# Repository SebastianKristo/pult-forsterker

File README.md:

<h1 align="center">Skjold</h1>

<p align="center"><b>Musikk i alle rom.</b><br>
Forsterkere, spillere og høyttalere som spiller sammen, styrt fra én app.<br>
Åpen programvare. Tegnet og bygget i Norge av Skjold Lab.</p>

<p align="center">
<a href="https://skjold-lab.com/">Nettside</a> ·
<a href="https://github.com/SebastianKristo/pult-forsterker/releases/latest">Last ned</a> ·
<a href="docs/TOTALINSTRUKS.md">Kom i gang</a> ·
<a href="docs/api/intro.md">API</a>
</p>

---

Skjold er et lydsystem du kan bygge selv. Hver enhet er en Raspberry Pi eller ESP32 med Skjold-programvaren, og alle
dukker opp i samme app. Spill det samme i hele huset, eller noe forskjellig i hvert rom.

## Produktene

| | Hva | Bygget på |
|---|---|---|
| **[Skjold S1](https://skjold-lab.com/s1/)** | Streamingforsterker for skrivebordet. 2 × 50 W, 4,58″ skjerm, USB-bryter for to PC-er. | Raspberry Pi 4, TPA3116D2 |
| **[Skjold Node](https://skjold-lab.com/node/)** | Liten nettverksspiller for rom som allerede har forsterker. | Raspberry Pi 4 eller 3B |
| **[Skjold Touch](https://skjold-lab.com/touch/)** | Spiller med 7″ berøringsskjerm. | Raspberry Pi 4, PCM5122 |
| **[Skjold Røst](https://skjold-lab.com/rost/)** | Aktiv høyttaler med grill hele veien rundt, skjerm og volumknott. | ESP32-S3 |
| **[Skjold Stav](https://skjold-lab.com/stav/)** | Fjernkontroll med 2,8″ berøringsskjerm, IR og ladedokk. | ESP32 (ESPHome) |
| **[Skjold Core](https://skjold-lab.com/core/)** | Bare programvaren, på en Raspberry Pi du allerede har. | Raspberry Pi 4 eller 3B |
| **Kassett, Hjul, Radio, Sans** | NFC-kassettspiller, dreieknapp-fjernkontroll, kjøkkenradio og romsensor. | ESP32 / Raspberry Pi |

## Dette kan den

- **Kilder:** AirPlay 2, Spotify Connect, Blåtann, internettradio, AUX og USB-lyd fra PC.
- **Bibliotek:** Navidrome, Plex, YouTube Music og Lyrion Music Server.
- **Flere rom:** synkron avspilling og grupper, med volum per rom.
- **Lyd:** equalizer per kilde, loudness og romkorreksjon med mikrofonen i telefonen.
- **Smarthus:** Home Assistant, Homey, Apple Hjem, Matter og MQTT. Enhetene finnes automatisk på nettverket.
- **Styring:** app for iPhone og Android, nettleser, knappene på enheten, fjernkontroll eller API.

## Kom i gang

1. **Last ned [Skjold Flasher](https://github.com/SebastianKristo/pult-forsterker/releases/latest)** for Mac, Windows eller Linux.
2. **Velg enhet** (S1, Touch, Node eller Core), skriv inn Wi-Fi og navn, og skriv SD-kortet.
3. **Sett kortet i Raspberry Pi-en.** Første oppstart installerer Skjold. Det tar 15–20 minutter.
4. **Åpne appen** eller `http://<navn>.local:8765` i nettleseren.

Hele veien fra SD-kort til smarthus står i [docs/TOTALINSTRUKS.md](docs/TOTALINSTRUKS.md).

Vil du installere for hånd på en ferdig Raspberry Pi OS?

```bash
git clone https://github.com/SebastianKristo/pult-forsterker.git && cd pult-forsterker
```

```bash
KI_AMP_BOARD=node bash pi/install.sh
```

Bytt `node` med `main` (S1), `touch` eller bruk `KI_AMP_CORE=1` for Core. Alle valgene står øverst i [`pi/install.sh`](pi/install.sh).

## Last ned

Alt ligger samlet i [siste utgivelse](https://github.com/SebastianKristo/pult-forsterker/releases/latest):

- **Skjold Flasher** (`.dmg`, `.exe`, `.AppImage`)
- **Android-appen** (`.apk`) og **iOS-appen** (usignert `.ipa`)
- **Filer til 3D-printer:** `skjold-3d-print.zip` med én mappe per produkt. Hver mappe har ferdige plater for Creality K2 (`.3mf`), enkeltdeler (STL), kilde (OpenSCAD) og egen `LES_MEG.md`
- **Bruksanvisning** (PDF) og **fastvare** for Røst

## Hva som ligger hvor

| Mappe | Innhold |
|---|---|
| [`pi/`](pi/) | Forsterkerprogrammet (`ki_amp_daemon.py`), installasjon, oppdatering og tester |
| [`skjold/app/`](skjold/app/) | Web-appen (Preact) og skjermbildet til Touch |
| [`skjold/ios/`](skjold/ios/), [`skjold/android/`](skjold/android/) | Appene for iPhone (SwiftUI) og Android (Compose) |
| [`skjold/flasher/`](skjold/flasher/) | Skjold Flasher (Electron) |
| [`skjold/os/`](skjold/os/) | Skjermprogrammet på S1 og Node |
| [`skjold/nettside/`](skjold/nettside/) | Nettsiden |
| [`kabinett/`](kabinett/) | 3D-modeller og utskriftsfiler. Hvert produkt har sin `LES_MEG.md` |
| [`pcb/`](pcb/), [`esphome/`](esphome/) | Kretskort og ESPHome-oppsett |
| [`custom_components/skjold/`](custom_components/skjold/), [`ha-kort/`](ha-kort/) | Home Assistant-integrasjonen og kortet (HACS) |
| [`homey/`](homey/) | Homey-appen |
| [`docs/`](docs/) | Veiledninger og [API-dokumentasjon](docs/api/intro.md) |

Flere veiledninger: [Skjold Touch](docs/SKJOLD_TOUCH.md) · [Oppsett-nett](docs/OPPSETT_NETT.md) · [Flere rom](docs/MULTIROOM.md) · [Skjold-hjem](docs/SKJOLD_HJEM.md) ·
[Fjernstyring](docs/FJERNSTYRING.md) · [Plugins](docs/PLUGINS.md) · [Proxmox og vanlig PC](docs/PROXMOX.md) ·
[Den første pultforsterkeren](docs/PULTFORSTERKER.md)

## Utvikling

```bash
cd pi && python3 -m pytest -q tests
```

```bash
cd skjold/app && npm ci && npm run dev
```

Web-appen kan kjøres mot en falsk enhet: `python3 skjold/ios/ci/mock_skjold.py 8765`, og åpne
`http://localhost:5173/?host=http://127.0.0.1:8765`.

## Status

Skjold er et byggeprosjekt og er ikke til salgs. Programvaren er i daglig bruk, men ikke alt er testet på alle
kombinasjoner av maskinvare. Finner du en feil, [meld den her](https://github.com/SebastianKristo/pult-forsterker/issues).

## Lisens

- **Programvare** (`pi/`, `skjold/app`, `skjold/os`, `skjold/flasher`, integrasjonene): MIT. Se [LICENSE](LICENSE).
- **Maskinvare, design og dokumentasjon** (`pcb/`, `kabinett/`, `skjold/design/` m.m.): CC BY-NC-SA 4.0. Du kan bygge
  selv, men ikke for salg. Se [LISENS-MASKINVARE.md](LISENS-MASKINVARE.md).
- **Nettsiden** (`skjold/nettside/`): alle rettigheter forbeholdt.

Full oversikt står i [LISENS.md](LISENS.md). Kommersiell lisens: jemtlands@proton.me

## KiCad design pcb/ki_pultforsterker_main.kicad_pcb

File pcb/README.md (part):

# Pultforsterker – hovedkort rev B

Ett kort (180 × 100 mm, 2 lag) som erstatter alle modulene, og som i tillegg har USB-delingsswitch, to AUX-innganger som
digitaliseres (så alt kan mikses), «smart relé» for strømmen til forsterkerdelen, hodetelefonutgang i fronten med
auto-demping, og plass til en 2,8" SPI-TFT med touch.
Raspberry Pi 4 kobles til med 40-pinners flatkabel; frontdelene med JST XH-plugger; alle bakkontakter er panelmonterte med
korte kabler til kortet.

**Status: rev B er ikke prøvd i praksis.** Kortet er tegnet og autorutet med KiCad 7 og Freerouting, DRC er fri for koblings- og
klaringsfeil, men ingen har bygget det. Regn med at første utgave kan trenge en jumper eller to. Programvaren for rev B (I2S-slave,
MCP23017, per-kilde-nivå, TFT) er skrevet, men kan bare testes på et ferdig kort.

## Blokker

| Blokk | Krets | Merknad |
|---|---|---|
| 24 V inn | skruterminal → sikring 5 A (5×20, THT) → reverspolaritets-FET → TVS SMBJ28A → 2 × 680–1000 µF/35 V Ø10 (THT, maks 16 mm høye) | KCD1 hovedbryter i serie utenfor kortet |
| 5 V / 5 A (alltid) | TPS54560 buck, 400 kHz, 10 µH, 3 × 47 µF, satt til 5,06 V (33k/6,2k) | Pi 4 («5V PI»), USB-hub, relé-spole |
| **Smart relé** | SRD-05VDC-SL-C (24 V → forsterker) + AO3401 P-MOSFET (5 V → 5V_SW) fra GPIO 27 via AO3400 | 5V_SW: LED-ringer, ADC-analog, TFT-baklys (PGA2311 og hodetelefonforsterkeren er alltid på, men mutet i standby). Av = helt stille og mørkt. Knapp bak på GPIO 15 |
| 3,3 V (alltid) | AMS1117-3.3 | MCP23017, pull-ups, encoder, **DAC, ADC-digital, oscillator, OLED og TFT-logikk** (Pi-ens I2C/SPI/I2S må aldri drive inn i strømløse kretser; skjermen slukkes i programvare) |
| 3,3 V_SW | AMS1117-3.3 fra 5V_SW | bare TFT-baklyset (Q9/Q10) |
| −5 V | LM2662 (FC = V+, 150 kHz) fra alltid-på 5 V, 10 µF inn/fly/ut | PGA2311 VA− (10–12 mA) |
| DAC | PCM5102A, I2S-slave, SCK = GND (intern PLL), FLT/DEMP/FMT = GND, XSMT fra GPIO 26 | 100 Ω + 2,2 nF ut |
| **ADC AUX 1** | PCM1808, I2S-master 256 fs fra 12,288 MHz-oscillator (48 kHz) | Pi-en er I2S-slave. Inngang 10k/10k-deler, 4,7 µF, 1 kΩ + 1 nF |
| **USB-kodek AUX 2** | PCM2900C, 12 MHz-krystall, bus-powered fra en USB-port på Pi-en (J19) | Inngang 10k/4,7k-deler, 4,7 µF. Vises som «USB Audio CODEC» |
| Volum | PGA2311 (±5 V), bit-banget fra GPIO 0 (SDI), 1 (SCLK), 16 (CS) – header 27/28/36, 5 V via ferritt + 10 µF | fast nivå; volum og nivå per kilde gjøres digitalt |
| Forsterker | TPA3116D2DAD, 26 dB (100k/20k), BD-modus (MODSEL = GND), 400 kHz (AM = 000), MUTE = GND, SYNC åpen, PLIMIT = GVDD, 10 µH + 680 nF + snubber per utgang | **Kjøleflaten er på toppen**: ingen loddepasta under, kjøleribbe 20 × 20 limes på. SDZ fra GPIO 22 |
| **USB-switch** | FE1.1s 4-ports hub + TS3USB221 2:1-mux (OE = GND). 2 × USB-C (PC 1/PC 2) på kortet, 4 × USB-A i venstre kant, polyfuse 2 A | Mux-valg fra MCP23017 GPB4 (S lav = PC 1). CC-pinnene har 5,1 k, så USB-C–USB-C-kabel virker. Huben og muxen går på alltid-5 V |
| I/O-ekspander | MCP23017 (I2C 0x20), INT → GPIO 14 | GPA0-4 knapper AIR/BT/AUX/USB/PWR, GPA5 jack-deteksjon, GPA6 HP-EN, GPB0-3 LED-ringer, GPB4 USB-mux, **GPB5 overtemperatur (NTC)**; GPA7 ligger på «EXP» men kan bare brukes som utgang (Microchip-errata: GPA7/GPB7 er ikke innganger) |
| **Overtemperaturvakt** | NTC 10 k (B 3950) på kjøleribben → J24 → 3,3 k-deler → 74LVC1G14 Schmitt-inverter (U14) → MCP GPB5. 100 k pull-down så «kald» hvis U14 mangler | Vipper ved ca. 75 °C, tilbake ved ca. 50 °C. Daemonen demper TPA3116 (SDZ) mens den er varm og melder i loggen/`/api/state` (`overtemp`) |
| LED-ringer | 5 × AO3400 low-side | POWER-ring på GPIO 12 (PWM) |
| **Hodetelefoner** | TPA6132A2 (DirectPath, +6 dB) etter PGA2311, 1 µF inn, alltid-på 5 V (EN kommer fra alltid-på MCP, og må aldri være høyere enn VDD). EN fra MCP23017 GPA6; jack-bryteren (DET) via 10 k til GPA5, 10 k pulldown på OUTL gir sikker «lav» uten plugg | 3,5 mm PJ-392 i fronten under POWER (J23). Ved innplugging dempes TPA3116 (SDZ) – kan slås av i HA/Homey |
| TFT | 14-pinners header (standard 2,4"/2,8" ILI9341/ST7789V-modul med XPT2046) | SPI0 CE0 (GPIO 8) = TFT, CE1 (GPIO 7) = touch med 10 k pull-up, DC 5, RST 6, IRQ 17, baklys GPIO 13 (PWM) via AO3400 + AO3401 fra 3V3_SW |

## GPIO-kart (hovedkort rev B)

| GPIO | Bruk | GPIO | Bruk |
|---|---|---|---|
| 2, 3 | I2C: OLED, MCP23017 | 18, 19, 21, 20 | I2S BCK, LRCK, DAC-data, ADC-data (Pi er slave) |
| 4 | OLED RES | 22 | TPA3116 SDZ (høy = på) |
| 5, 6, 13 | TFT DC, RST, baklys (PWM) | 23, 24, 25 | encoder CLK, DT, SW |
| 7, 8 | SPI0 CE1 touch, CE0 TFT | 26 | DAC XSMT |
| 0, 1 (header 27/28) | PGA2311 SDI, SCLK (ID-EEPROM-pinnene – ingen HAT-EEPROM på kortet) | 16 | PGA2311 CS |
| 9, 10, 11 | SPI0 MISO (bare touch – TFT-ens SDO er ikke koblet), MOSI, SCLK | 27 | strømrelé + 5V_SW |
| 12 | POWER-ring (PWM) | | |
| 14 | MCP23017 INT | 15 | strømknapp bak |
| 17 | touch IRQ | | |

Sett `KI_AMP_BOARD=main` i `/etc/ki-amp.env` (gjøres av `KI_AMP_BOARD=main bash install.sh`).

## Kontakter

| Ref | Type | Pinner |
|---|---|---|
| J1 | skruterminal 5,08 | 24 V +, GND (fra DC-099 via KCD1) |
| J2 / J3 | skruterminal 5,08 | SPK L + −, SPK R + − |
| J4 / J20 | JST XH 3 | AUX 1 / AUX 2: L, R, GND (fra PJ392 bak) |
| J5 | 2×20 header | Raspberry Pi 40-pin (flatkabel 15–20 cm). Pi-en skrus under kortet i H5–H8 (M2,5, 20 mm avstandsstykker), portene mot høyre |
| J6 | skruterminal 5,08 | 5 V, GND → Pi 4 header pinne 2/6 (18 AWG) |
| J7 | JST XH 6 | knapp 1 «BT» (AirPlay + Bluetooth), knapp 2 «RADIO», AUX, USB, POWER, GND (bryterne) |
| J8 | JST XH 5 | CLK, DT, SW, 3V3, GND (encoder) |
| J9 | JST XH 5 | 3V3_SW, GND, SDA, SCL, RES (OLED) |
| J10 | JST XH 6 | 5V_SW, AIR−, BT−, AUX−, USB−, POWER− (LED-ringer) |
| J11 / J12 | USB-C på kortet, i bakkanten (åpningen mot bakpanelet) | PC 1 / PC 2 → panelmontert USB-C bak; panelkabelens hann-plugg settes rett i, 15–20 cm |
| J13 | 1×14 header 2,54 | TFT: VCC GND CS RST DC MOSI SCK LED (MISO ikke koblet) T_CLK T_CS T_DIN T_DO T_IRQ (samme rekkefølge som modulen) |
| J15–J18 | USB-A | 4 × USB-A ut gjennom venstre vegg |
| J19 | JST XH 4 | 5V, D−, D+, GND fra en USB-A-port på Pi-en (USB-kodeken) |
| J21 | JST XH 2 | strømknapp bak (momentan), GND |
| J22 | JST XH 6 | EXP: MCP GPA5 (= jack-deteksjon via 10 k), GPA6 (= HP-EN), GPA7 (ledig, bare utgang), GPB5 (= overtemperatur fra U14 – ikke driv den), 3V3, GND |
| J24 | JST XH 2 | NTC 10 k (B 3950) festet på kjøleribben (ikke polarisert) |
| J23 | JST XH 4 | Hodetelefonjack i fronten (PJ392 med bryter, under POWER): L, R, GND, DET (jackens bryterkontakt for L: ligger mot L uten plugg, åpen med plugg) |

## Filer

- `build_board.py` – hele kortet (deler, netliste, plassering) som Python mot pcbnew. Kjør for å regenerere `.kicad_pcb`.
- `build_schematic.py` – lager skjemaet `ki_pultforsterker_main.kicad_sch` (ett A1-ark, delene gruppert i blokker, globale etiketter med nettnavnene) fra kortet, pluss egne symboler i `ki_pultforsterker.kicad_sym`; verifiserer netlisten pinne for pinne mot `.kicad_pcb` (må gi 0 avvik), kjører ERC og lager `produksjon/skjema.pdf`/`.svg`. Kjør `python3 build_schematic.py` for å regenerere (etter `build_board.py`/`export.py`).
- `route.py` – eksporterer DSN og kjører Freerouting (`FREEROUTING=/sti/freerouting.jar python3 route.py`).
- `export.py` – importerer SES, fyller GND-soner, kjører DRC, lager `produksjon/`.
- `produksjon/ki_pultforsterker_main_gerber.zip` – last opp til JLCPCB/PCBWay (2 lag, 1,6 mm, HASL eller ENIG, 1 oz).
- `produksjon/ki_pultforsterker_main_bom.csv` + `_cpl.csv` – for SMT-montering (LCSC-numre).
- `bom.csv` – full deleliste per referanse.

## Bestilling

1. JLCPCB → «Add gerber file» → zip-en. 2 lag, 180 × 100 mm, grønn/svart, HASL (lead free).
2. Huk av «PCB Assembly», Top side, 2 stk. Last opp BOM og CPL.
3. Kontroller at alle LCSC-numre finnes på lager; bytt tilsvarende hvis noen er tomme (verdiene står i BOM). Alle koder i BOM-en er
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
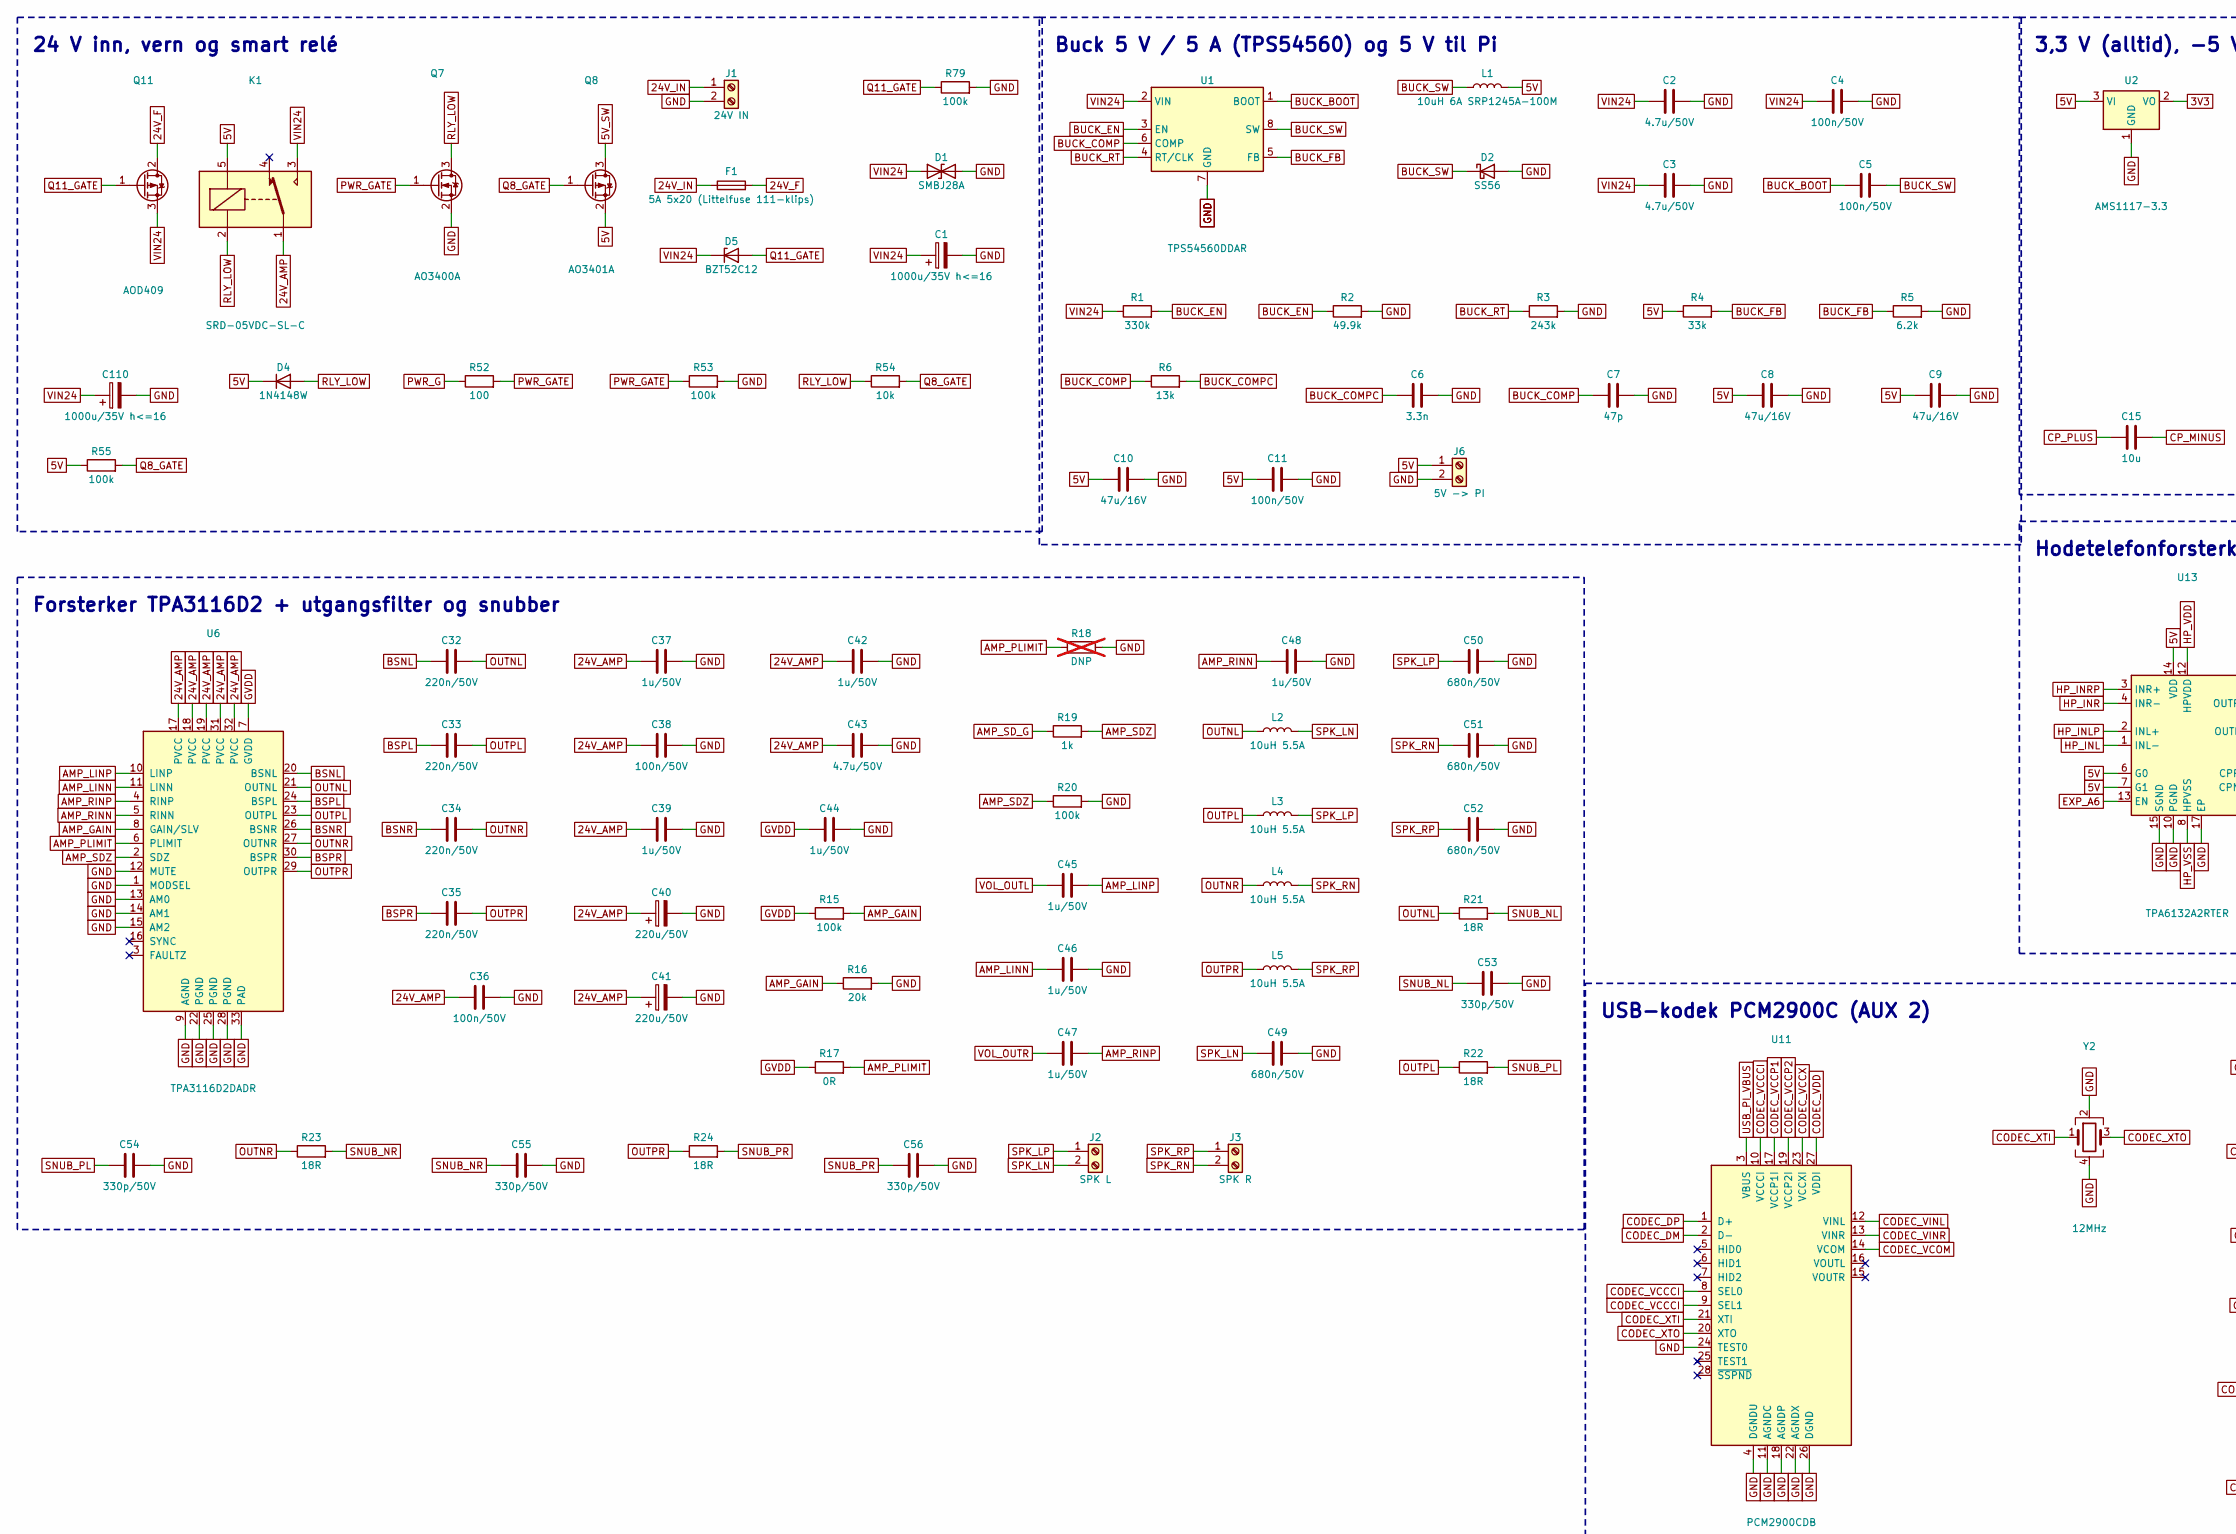
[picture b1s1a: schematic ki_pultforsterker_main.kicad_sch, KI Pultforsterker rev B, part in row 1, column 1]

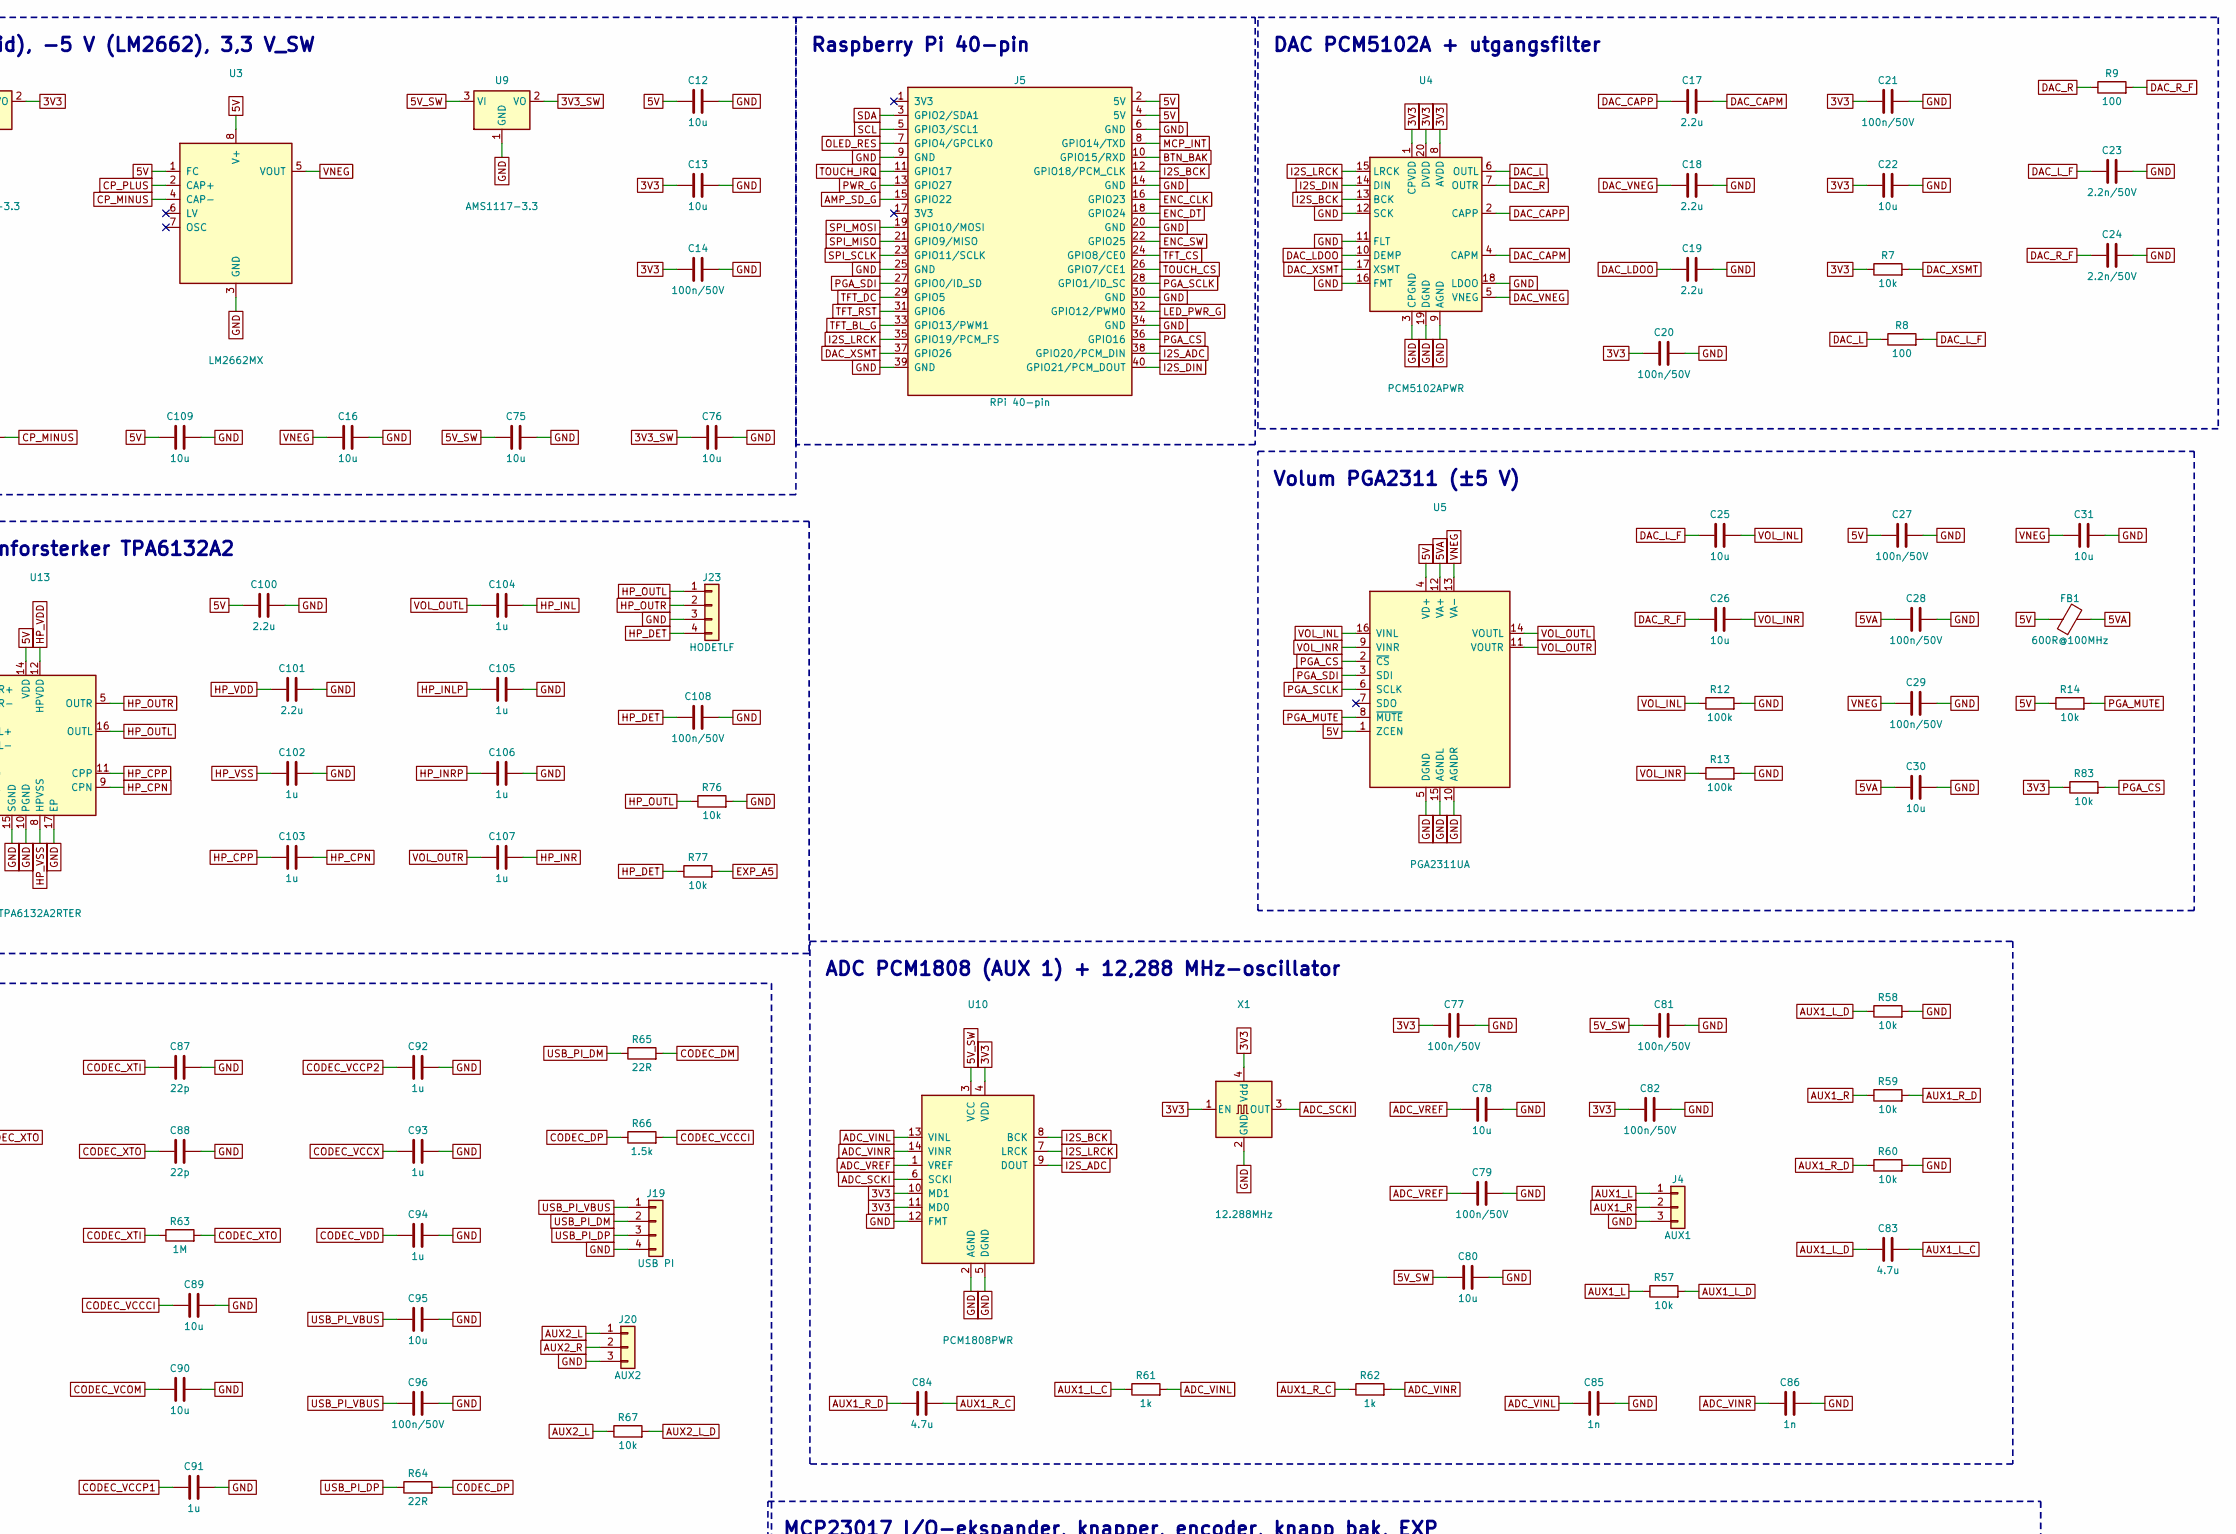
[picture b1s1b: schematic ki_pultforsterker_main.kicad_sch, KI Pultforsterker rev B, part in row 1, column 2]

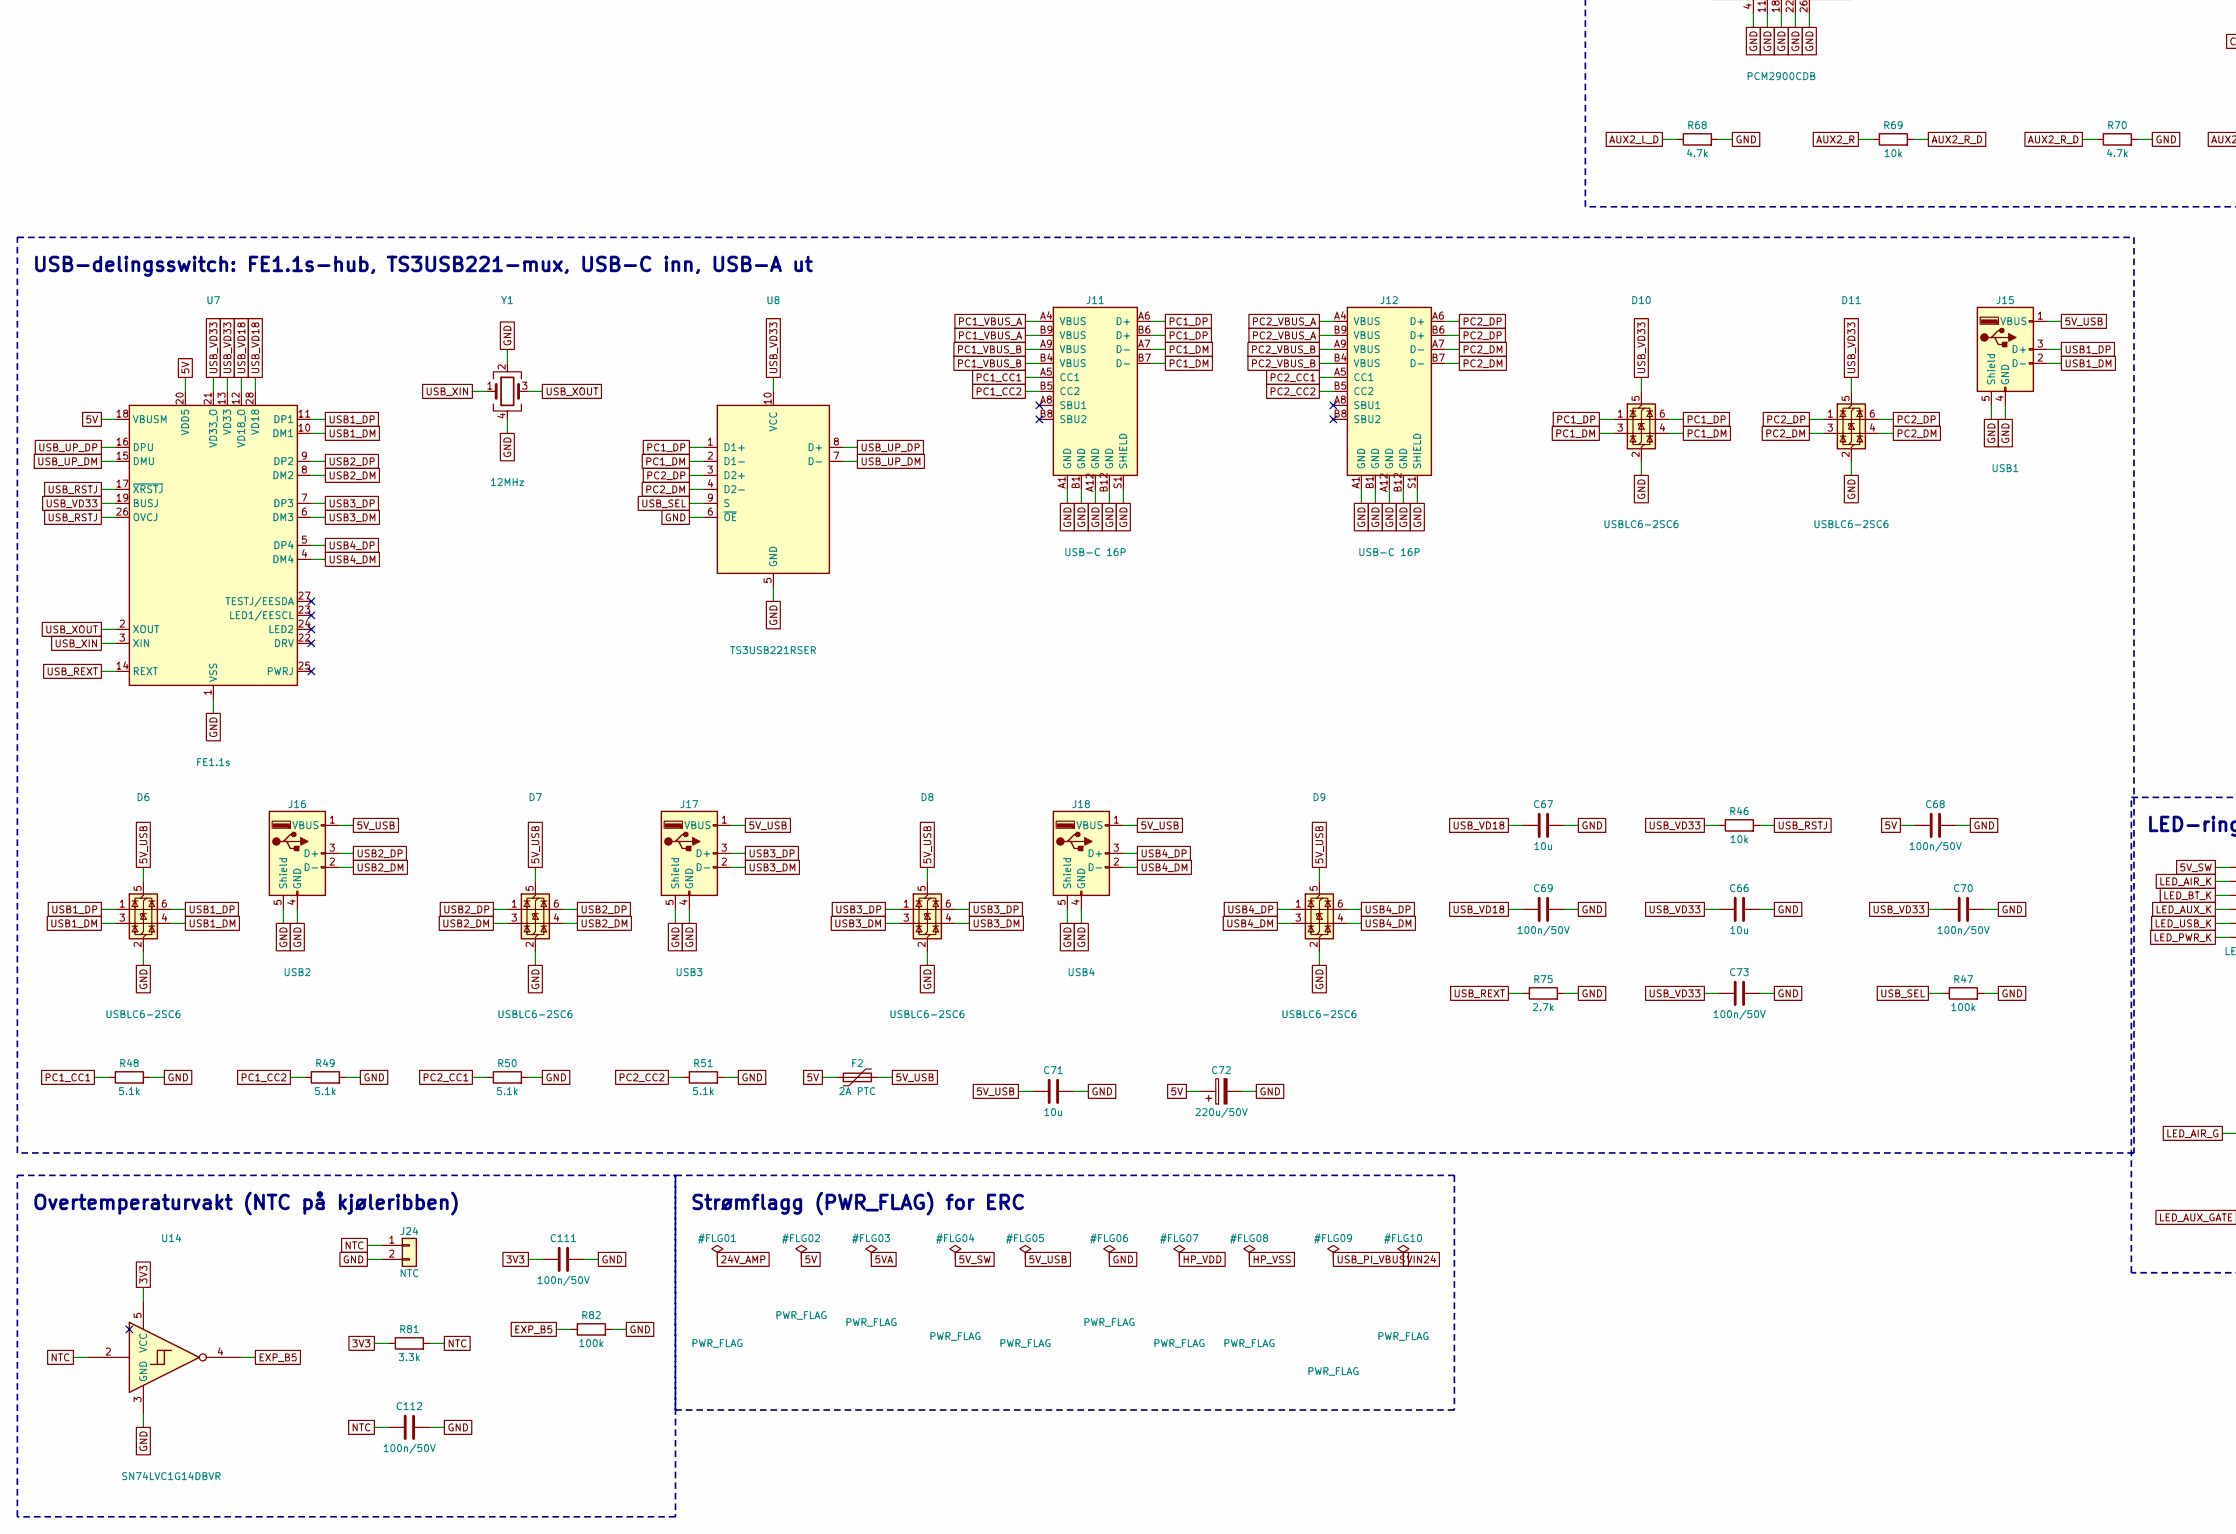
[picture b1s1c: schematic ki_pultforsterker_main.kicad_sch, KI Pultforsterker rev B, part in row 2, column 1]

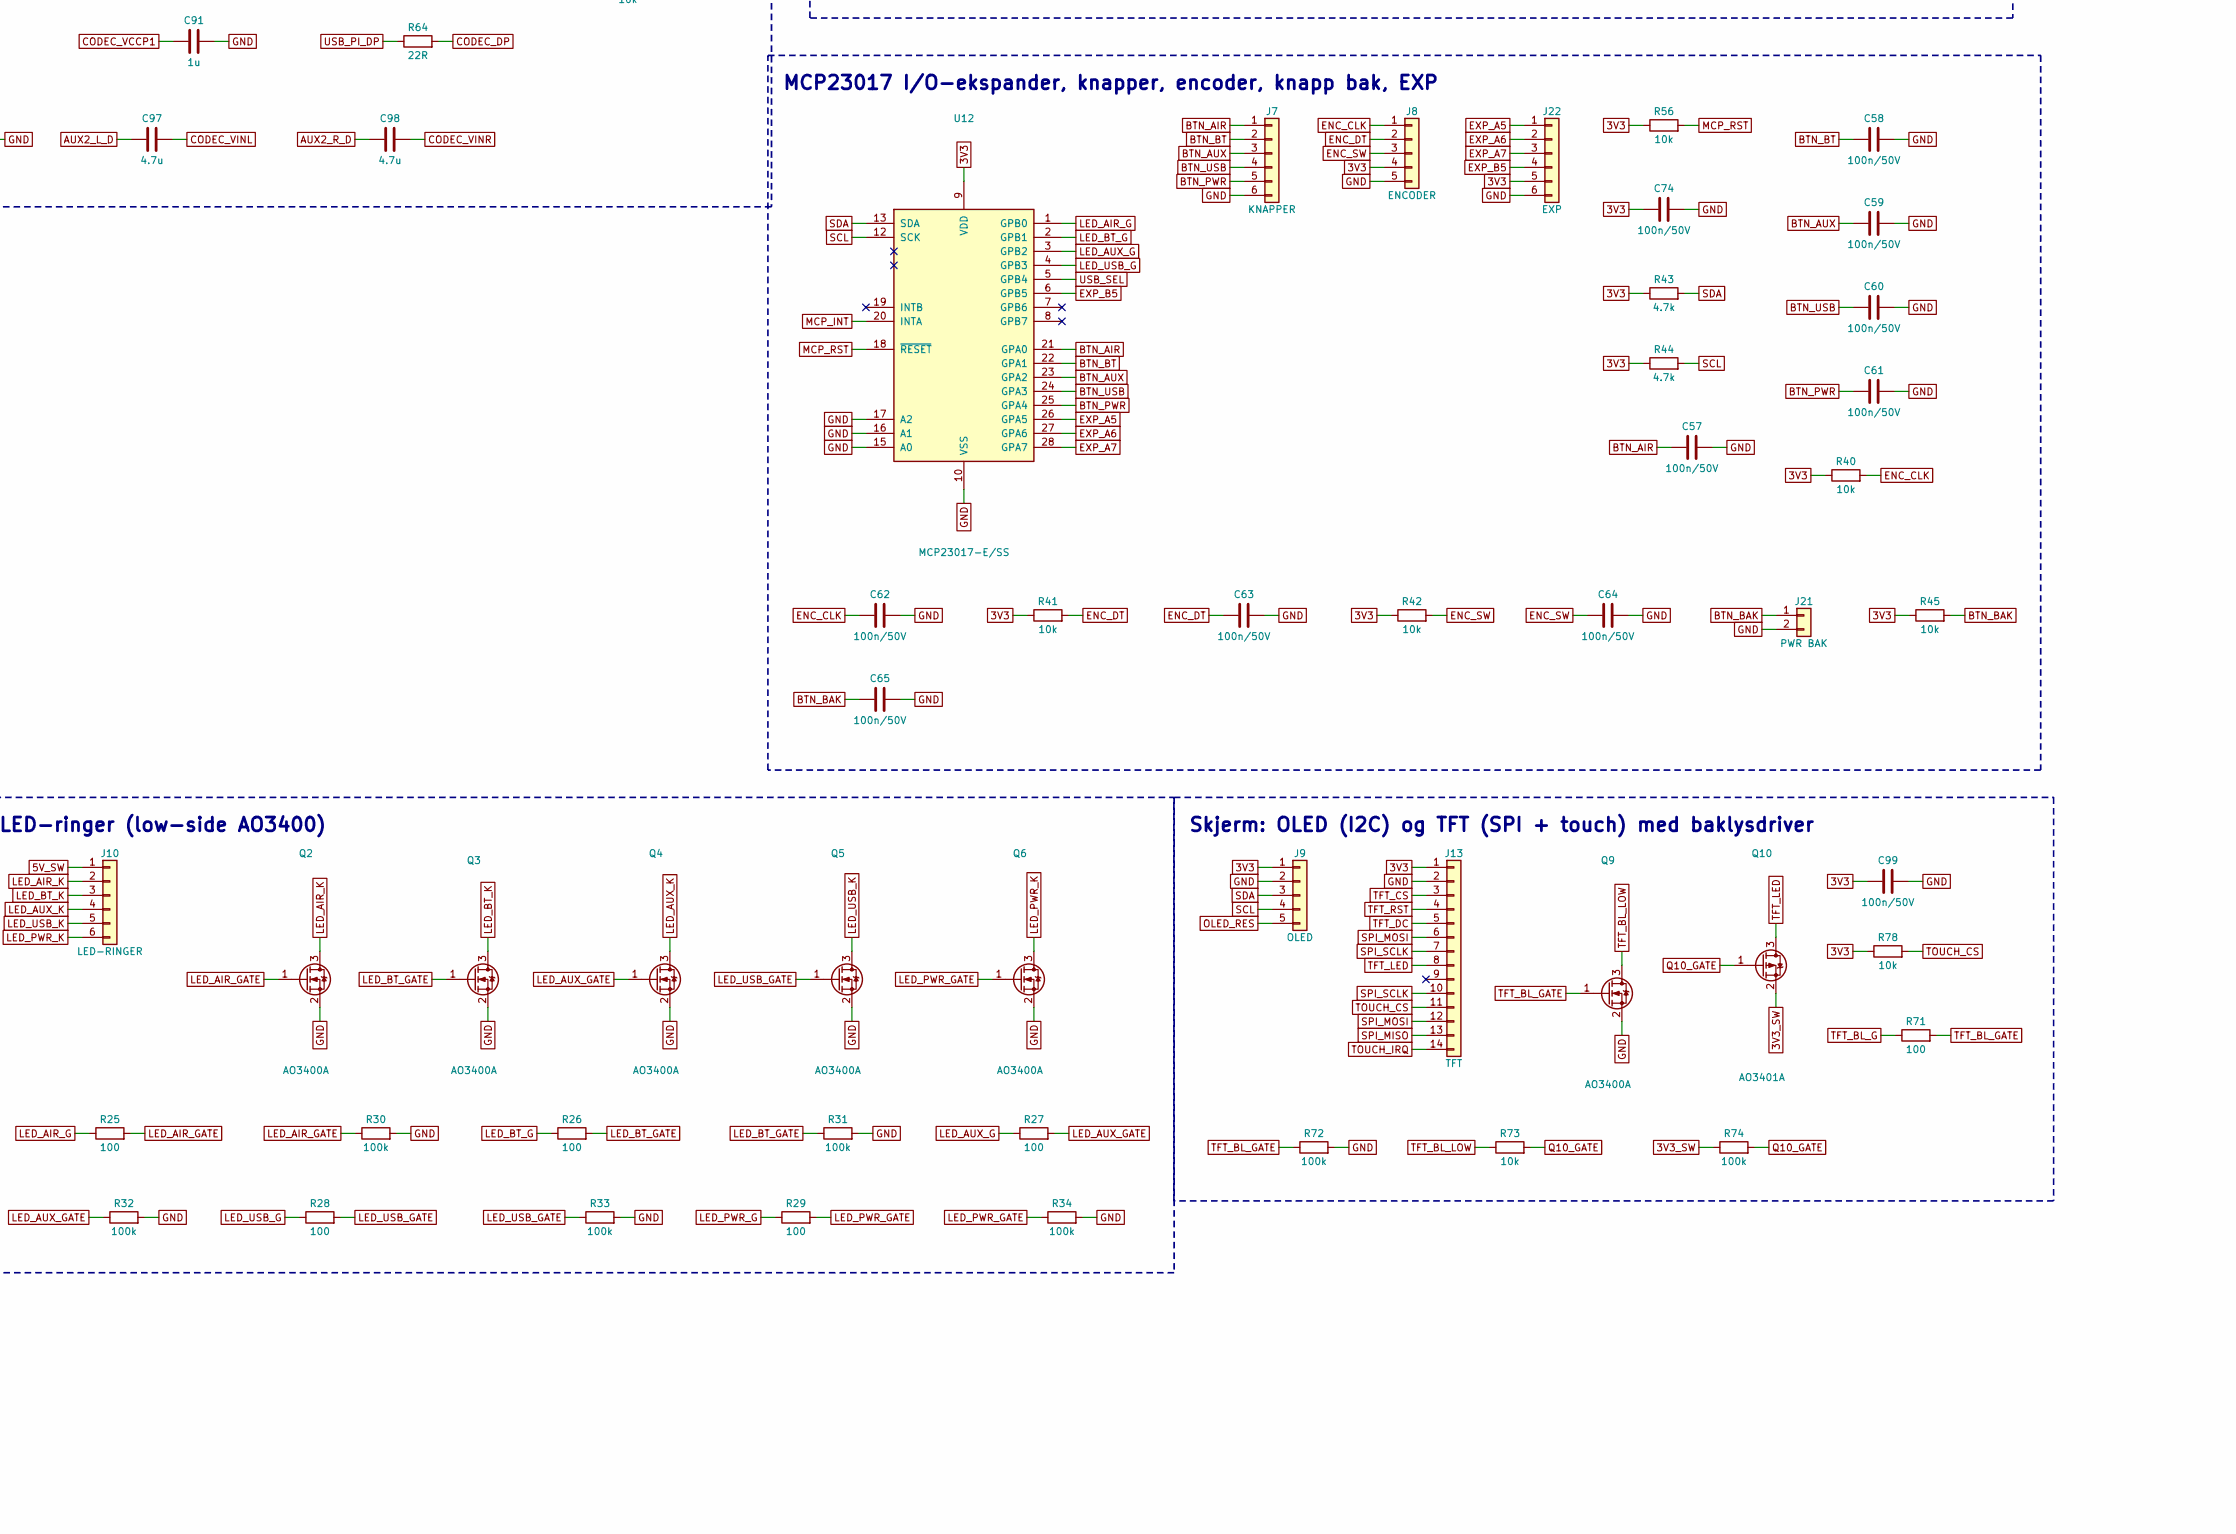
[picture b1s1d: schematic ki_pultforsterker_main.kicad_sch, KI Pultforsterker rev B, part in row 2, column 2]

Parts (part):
C1, C110: 1000u/35V h<=16; CP_Radial_D10.0mm_P5.00mm
C2, C3, C43: 4.7u/50V; C_1210_3225Metric; LCSC C170099
C4, C5, C11, C14, C20, C21, C27, C28, C29, C36, C38, C57, C58, C59, C60, C61, C62, C63, C64, C65, C68, C69, C70, C73, C74, C77, C79, C81, C82, C96, C99, C108, C111, C112: 100n/50V; C_0603_1608Metric; LCSC C14663
C6: 3.3n; C_0603_1608Metric; LCSC C1613
C7: 47p; C_0603_1608Metric; LCSC C1671
C8, C9, C10: 47u/16V; C_1210_3225Metric; LCSC C77101
C12, C13, C15, C16, C22, C30, C31, C66, C67, C75, C76, C78, C80, C89, C90, C95, C109: 10u; C_0805_2012Metric; LCSC C15850
C17, C18, C19, C100, C101: 2.2u; C_0603_1608Metric; LCSC C23630
C23, C24: 2.2n/50V; C_0603_1608Metric; LCSC C1604
C25, C26, C71: 10u; C_1206_3216Metric; LCSC C13585
C32, C33, C34, C35: 220n/50V; C_0805_2012Metric; LCSC C5378
C37, C39, C42, C44, C45, C46, C47, C48: 1u/50V; C_0805_2012Metric; LCSC C28323
C40, C41, C72: 220u/50V; CP_Elec_10x10.5; LCSC C190286
C49, C50, C51, C52: 680n/50V; C_1206_3216Metric; LCSC C1881
C53, C54, C55, C56: 330p/50V; C_0603_1608Metric; LCSC C1664
C83, C84, C97, C98: 4.7u; C_0805_2012Metric; LCSC C1779
C85, C86: 1n; C_0603_1608Metric; LCSC C1588
C87, C88: 22p; C_0603_1608Metric; LCSC C1653
C91, C92, C93, C94, C102, C103, C104, C105, C106, C107: 1u; C_0603_1608Metric; LCSC C15849
D1: SMBJ28A; D_SMB; LCSC C20623778
D2: SS56; D_SMB; LCSC C4154973
D4: 1N4148W; D_SOD-123; LCSC C81598
D5: BZT52C12; D_SOD-123; LCSC C43491
D6, D7, D8, D9, D10, D11: USBLC6-2SC6; SOT-23-6; LCSC C7519
F1: 5A 5x20 (Littelfuse 111-klips); Fuseholder_Clip-5x20mm_Littelfuse_111_Inline_P20.00x5.00mm_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; LCSC C151075
F2: 2A PTC; Fuse_1812_4532Metric; LCSC C545213
FB1: 600R@100MHz; L_0805_2012Metric; LCSC C18305
J1: 24V IN; TerminalBlock_bornier-2_P5.08mm; LCSC C8465
J2: SPK L; TerminalBlock_bornier-2_P5.08mm; LCSC C8465
J3: SPK R; TerminalBlock_bornier-2_P5.08mm; LCSC C8465
J4: AUX1; JST_XH_B3B-XH-A_1x03_P2.50mm_Vertical; LCSC C144394
J5: RPi 40-pin; PinHeader_2x20_P2.54mm_Vertical; LCSC C50980
J6: 5V -> PI; TerminalBlock_bornier-2_P5.08mm; LCSC C8465
J7: KNAPPER; JST_XH_B6B-XH-A_1x06_P2.50mm_Vertical; LCSC C144397
J8: ENCODER; JST_XH_B5B-XH-A_1x05_P2.50mm_Vertical; LCSC C157991
J9: OLED; JST_XH_B5B-XH-A_1x05_P2.50mm_Vertical; LCSC C157991
J10: LED-RINGER; JST_XH_B6B-XH-A_1x06_P2.50mm_Vertical; LCSC C144397
J11, J12: USB-C 16P; USB_C_Receptacle_HRO_TYPE-C-31-M-12; LCSC C165948
J13: TFT; PinHeader_1x14_P2.54mm_Vertical; LCSC C50981
J15: USB1; USB_A_Molex_67643_Horizontal; LCSC C2765194
J16: USB2; USB_A_Molex_67643_Horizontal; LCSC C2765194
J17: USB3; USB_A_Molex_67643_Horizontal; LCSC C2765194
J18: USB4; USB_A_Molex_67643_Horizontal; LCSC C2765194
J19: USB PI; JST_XH_B4B-XH-A_1x04_P2.50mm_Vertical; LCSC C144395
J20: AUX2; JST_XH_B3B-XH-A_1x03_P2.50mm_Vertical; LCSC C144394
J21: PWR BAK; JST_XH_B2B-XH-A_1x02_P2.50mm_Vertical; LCSC C158012
J22: EXP; JST_XH_B6B-XH-A_1x06_P2.50mm_Vertical; LCSC C144397
J23: HODETLF; JST_XH_B4B-XH-A_1x04_P2.50mm_Vertical; LCSC C144395
J24: NTC; JST_XH_B2B-XH-A_1x02_P2.50mm_Vertical; LCSC C158012
K1: SRD-05VDC-SL-C; Relay_SPDT_SANYOU_SRD_Series_Form_C; LCSC C35449
L1: 10uH 6A SRP1245A-100M; L_Bourns_SRP1245A; LCSC C2042471
L2, L3, L4, L5: 10uH 5.5A; L_12x12mm_H8mm; LCSC C3221699
Q2, Q3, Q4, Q5, Q6, Q7, Q9: AO3400A; SOT-23-3; LCSC C20917
Q8, Q10: AO3401A; SOT-23-3; LCSC C15127
Q11: AOD409; TO-252-2; LCSC C36220
R1: 330k; R_0603_1608Metric; LCSC C23137
R2: 49.9k; R_0603_1608Metric; LCSC C23184
R3: 243k; R_0603_1608Metric; LCSC C100895
R4: 33k; R_0603_1608Metric; LCSC C4216
R5: 6.2k; R_0603_1608Metric; LCSC C4260
R6: 13k; R_0603_1608Metric; LCSC C22797
R7, R14, R40, R41, R42, R45, R46, R54, R56, R57, R58, R59, R60, R67, R69, R73, R76, R77, R78, R83: 10k; R_0603_1608Metric; LCSC C25804
R8, R9, R25, R26, R27, R28, R29, R52, R71: 100; R_0603_1608Metric; LCSC C22775
R12, R13, R15, R20, R30, R31, R32, R33, R34, R47, R53, R55, R72, R74, R79, R82: 100k; R_0603_1608Metric; LCSC C25803
R16: 20k; R_0603_1608Metric; LCSC C4184
R17: 0R; R_0603_1608Metric; LCSC C21189
R18: DNP; R_0603_1608Metric; not fitted
R19, R61, R62: 1k; R_0603_1608Metric; LCSC C21190
R21, R22, R23, R24: 18R; R_1206_3216Metric; LCSC C2907439
R43, R44, R68, R70: 4.7k; R_0603_1608Metric; LCSC C23162
R48, R49, R50, R51: 5.1k; R_0603_1608Metric; LCSC C23186
R63: 1M; R_0603_1608Metric; LCSC C22935
R64, R65: 22R; R_0603_1608Metric; LCSC C23345
R66: 1.5k; R_0603_1608Metric; LCSC C22843
R75: 2.7k; R_0603_1608Metric; LCSC C13167
R81: 3.3k; R_0603_1608Metric; LCSC C22978
U1: TPS54560DDAR; HSOP-8-1EP_3.9x4.9mm_P1.27mm_EP2.3x2.3mm; LCSC C31966
U2, U9: AMS1117-3.3; SOT-223-3_TabPin2; LCSC C6186
U3: LM2662MX; SOIC-8_3.9x4.9mm_P1.27mm; LCSC C129316
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
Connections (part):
3V3: C13.1, C14.1, C20.1, C21.1, C22.1, C74.1, C77.1, C82.1, C99.1, C111.1, J8.4, J9.1, J13.1, J22.5, R7.1, R40.1, R41.1, R42.1, R43.1, R44.1, R45.1, R56.1, R78.1, R81.1, R83.1, U2.2 (VO), U4.1 (CPVDD), U4.8 (AVDD), U4.20 (DVDD), U10.4 (VDD), U10.10 (MD1), U10.11 (MD0), U12.9 (VDD), U14.5 (VCC), X1.1 (EN), X1.4 (Vdd)
3V3_SW: C76.1, Q10.2 (S), R74.1, U9.2 (VO)
5V: C8.1, C9.1, C10.1, C11.1, C12.1, C27.1, C68.1, C72.1, C100.1, C109.1, D4.1 (K), F2.1, FB1.1, J5.2 (5V), J5.4 (5V), J6.1, K1.5, L1.2, Q8.2 (S), R4.1, R14.1, R55.1, U2.3 (VI), U3.1 (FC), U3.8 (V+), U5.1 (ZCEN), U5.4 (VD+), U7.18 (VBUSM), U7.20 (VDD5), U13.6 (G0), U13.7 (G1), U13.14 (VDD)
5VA: C28.1, C30.1, FB1.2, U5.12 (VA+)
5V_SW: C75.1, C80.1, C81.1, J10.1, Q8.3 (D), U9.3 (VI), U10.3 (VCC)
5V_USB: C71.1, D6.5 (VBUS), D7.5 (VBUS), D8.5 (VBUS), D9.5 (VBUS), F2.2, J15.1 (VBUS), J16.1 (VBUS), J17.1 (VBUS), J18.1 (VBUS)
24V_AMP: C36.1, C37.1, C38.1, C39.1, C40.1, C41.1, C42.1, C43.1, K1.1, U6.17 (PVCC), U6.18 (PVCC), U6.19 (PVCC), U6.31 (PVCC), U6.32 (PVCC)
24V_F: F1.2, Q11.2 (D)
24V_IN: F1.1, J1.1
ADC_SCKI: U10.6 (SCKI), X1.3 (OUT)
ADC_VINL: C85.1, R61.2, U10.13 (VINL)
ADC_VINR: C86.1, R62.2, U10.14 (VINR)
ADC_VREF: C78.1, C79.1, U10.1 (VREF)
AMP_GAIN: R15.2, R16.1, U6.8 (GAIN/SLV)
AMP_LINN: C46.1, U6.11 (LINN)
AMP_LINP: C45.2, U6.10 (LINP)
AMP_PLIMIT: R17.2, R18.1, U6.6 (PLIMIT)
AMP_RINN: C48.1, U6.5 (RINN)
AMP_RINP: C47.2, U6.4 (RINP)
AMP_SDZ: R19.2, R20.1, U6.2 (SDZ)
AMP_SD_G: J5.15 (GPIO22), R19.1
AUX1_L: J4.1, R57.1
AUX1_L_C: C83.2, R61.1
AUX1_L_D: C83.1, R57.2, R58.1
AUX1_R: J4.2, R59.1
AUX1_R_C: C84.2, R62.1
AUX1_R_D: C84.1, R59.2, R60.1
AUX2_L: J20.1, R67.1
AUX2_L_D: C97.1, R67.2, R68.1
AUX2_R: J20.2, R69.1
AUX2_R_D: C98.1, R69.2, R70.1
BSNL: C32.1, U6.20 (BSNL)
BSNR: C34.1, U6.26 (BSNR)
BSPL: C33.1, U6.24 (BSPL)
BSPR: C35.1, U6.30 (BSPR)
BTN_AIR: C57.1, J7.1, U12.21 (GPA0)
BTN_AUX: C59.1, J7.3, U12.23 (GPA2)
BTN_BAK: C65.1, J5.10 (GPIO15/RXD), J21.1, R45.2
BTN_BT: C58.1, J7.2, U12.22 (GPA1)
BTN_PWR: C61.1, J7.5, U12.25 (GPA4)
BTN_USB: C60.1, J7.4, U12.24 (GPA3)
BUCK_BOOT: C5.1, U1.1 (BOOT)
BUCK_COMP: C7.1, R6.1, U1.6 (COMP)
BUCK_COMPC: C6.1, R6.2
BUCK_EN: R1.2, R2.1, U1.3 (EN)
BUCK_FB: R4.2, R5.1, U1.5 (FB)
BUCK_RT: R3.1, U1.4 (RT/CLK)
BUCK_SW: C5.2, D2.1 (K), L1.1, U1.8 (SW)
CODEC_DM: R65.2, U11.2 (D-)
CODEC_DP: R64.2, R66.1, U11.1 (D+)
CODEC_VCCCI: C89.1, R66.2, U11.8 (SEL0), U11.9 (SEL1), U11.10 (VCCCI)
CODEC_VCCP1: C91.1, U11.17 (VCCP1I)
CODEC_VCCP2: C92.1, U11.19 (VCCP2I)
CODEC_VCCX: C93.1, U11.23 (VCCXI)
CODEC_VCOM: C90.1, U11.14 (VCOM)
CODEC_VDD: C94.1, U11.27 (VDDI)
CODEC_VINL: C97.2, U11.12 (VINL)
CODEC_VINR: C98.2, U11.13 (VINR)
CODEC_XTI: C87.1, R63.1, U11.21 (XTI), Y2.1
CODEC_XTO: C88.1, R63.2, U11.20 (XTO), Y2.3
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
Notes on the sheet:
24 V inn, vern og smart relé
Buck 5 V / 5 A (TPS54560) og 5 V til Pi
3,3 V (alltid), −5 V (LM2662), 3,3 V_SW
Raspberry Pi 40-pin
DAC PCM5102A + utgangsfilter
Volum PGA2311 (±5 V)
Hodetelefonforsterker TPA6132A2
Forsterker TPA3116D2 + utgangsfilter og snubber
ADC PCM1808 (AUX 1) + 12,288 MHz-oscillator
USB-kodek PCM2900C (AUX 2)
USB-delingsswitch: FE1.1s-hub, TS3USB221-mux, USB-C inn, USB-A ut
MCP23017 I/O-ekspander, knapper, encoder, knapp bak, EXP
LED-ringer (low-side AO3400)
Skjerm: OLED (I2C) og TFT (SPI + touch) med baklysdriver
Overtemperaturvakt (NTC på kjøleribben)
Strømflagg (PWR_FLAG) for ERC

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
